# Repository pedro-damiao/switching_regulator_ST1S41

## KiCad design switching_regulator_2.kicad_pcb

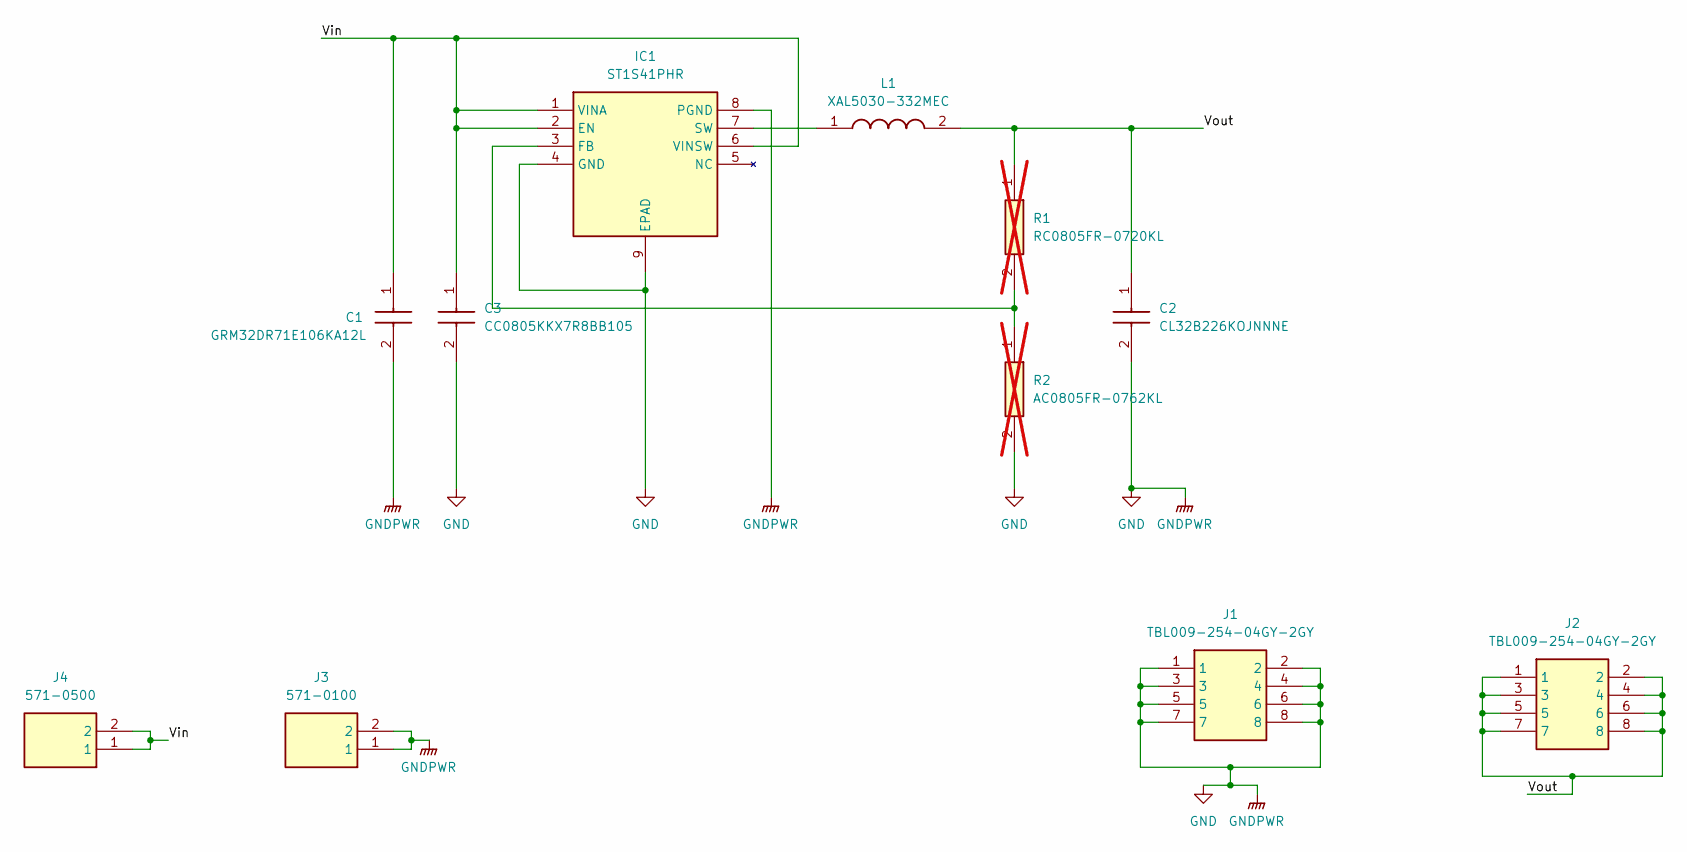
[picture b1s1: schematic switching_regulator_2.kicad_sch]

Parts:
C1: GRM32DR71E106KA12L; GRM32DR61C106KA01L; Mouser Part Number 81-GRM32DR71E106KA12
C2: CL32B226KOJNNNE; INDC3225X280N; Mouser Part Number 187-CL32B226KOJNNNE
C3: CC0805KKX7R8BB105; CAPC2012X145N; Mouser Part Number 603-CC805KKX7R8BB105
IC1: ST1S41PHR; SOIC127P600X170-9N; Mouser Part Number 511-ST1S41PHR
J1, J2: TBL009-254-04GY-2GY; TBL00925404GY2GY; Mouser Part Number 490-TBL00925404GY2GY
J3: 571-0100; 5710100; Mouser Part Number 164-6218
J4: 571-0500; 5710500; Mouser Part Number 164-6219
L1: XAL5030-332MEC; XAL5030332MEC; Mouser Part Number 994-XAL5030-332MEC
R1: RC0805FR-0720KL; RESC2012X60N; Mouser Part Number 603-RC0805FR-0720KL; not fitted
R2: AC0805FR-0762KL; RESC2012X60N; Mouser Part Number 603-RC0805FR-0720KL; not fitted

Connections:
/Vin: C1.1, C3.1, IC1.1 (VINA), IC1.2 (EN), IC1.6 (VINSW), J4.1, J4.2
/Vout: C2.1, J2.1, J2.2, J2.3, J2.4, J2.5, J2.6, J2.7, J2.8, L1.2, R1.1
GND: C1.2, C2.2, C3.2, IC1.4 (GND), IC1.8 (PGND), IC1.9 (EPAD), J1.1, J1.2, J1.3, J1.4, J1.5, J1.6, J1.7, J1.8, J3.1, J3.2, R2.2
unnamed: IC1.3 (FB), R1.2, R2.1
unnamed: IC1.7 (SW), L1.1

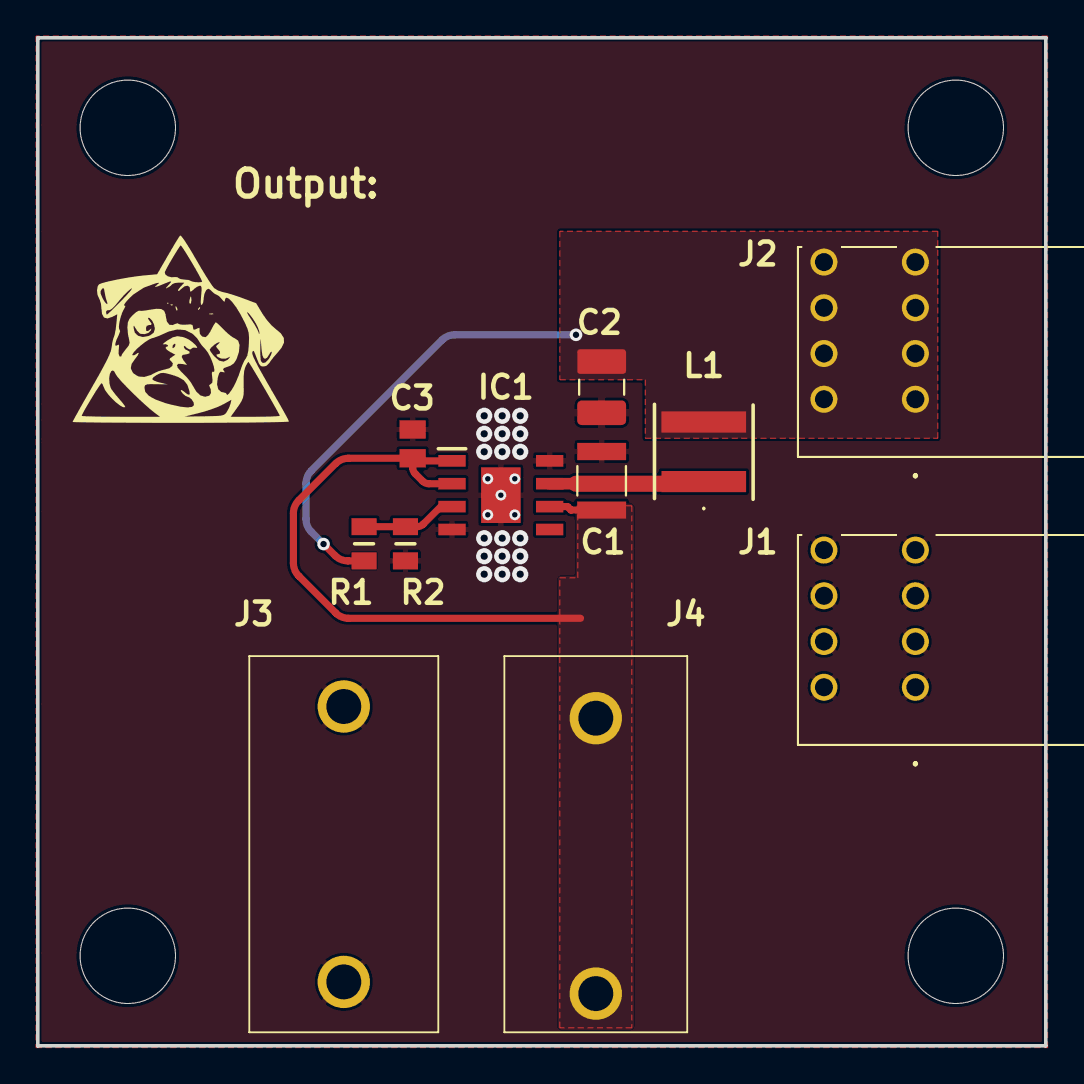
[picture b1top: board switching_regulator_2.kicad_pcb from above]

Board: 2 copper layers, 56.0 x 56.0 mm, 12 parts (0 on the bottom side), 5 nets.

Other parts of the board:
Output:: LOGO; pulga_logo

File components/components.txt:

Total 11

Connectors
1x Banana socket Red: 571-0100
1x Banana socket Black: 571-0500
2x Terminal Block 4 pins duplicated: TBL009-254-04GY-2GY

Passive
1x Inductor: XAL5030-332EMC
1x Resistor: RC0805FR-0720KL
1x Resistor: AC0805FR-0762KL
1x Capacitor: CC0805KKX7R8BB105
1x Capacitor: GRM32DR71E106KA12L
1x Capacitor: CL32B226KOJNNNE

IC
1x ST1S41PHR: Switching regulator

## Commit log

2026-03-15 Initial commit: switching_regulator_2 KiCad project
2026-03-18 [ADD] components to the projects itself
2026-03-18 [UPD] PCB vias and traces sizes
2026-03-18 [ADD] logos
2026-03-18 [ADD] curved tracks
2026-03-18 [ADD] gerber, drill, boom, placement files
2026-04-23 [UPD] to Kicad 10.0
